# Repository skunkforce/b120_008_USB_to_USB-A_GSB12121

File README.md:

# edgy_board number b120
This design is part of the [edgy board project](https://github.com/skunkforce/edgy_boards). 

# getting started
This repository uses submodules. After cloning use the command 

```$ git submodule update --init --recursive```

to pull the submodules before opening the project with kicad. 

# Tests
Tests can be found in [TESTS.md](TESTS.md)

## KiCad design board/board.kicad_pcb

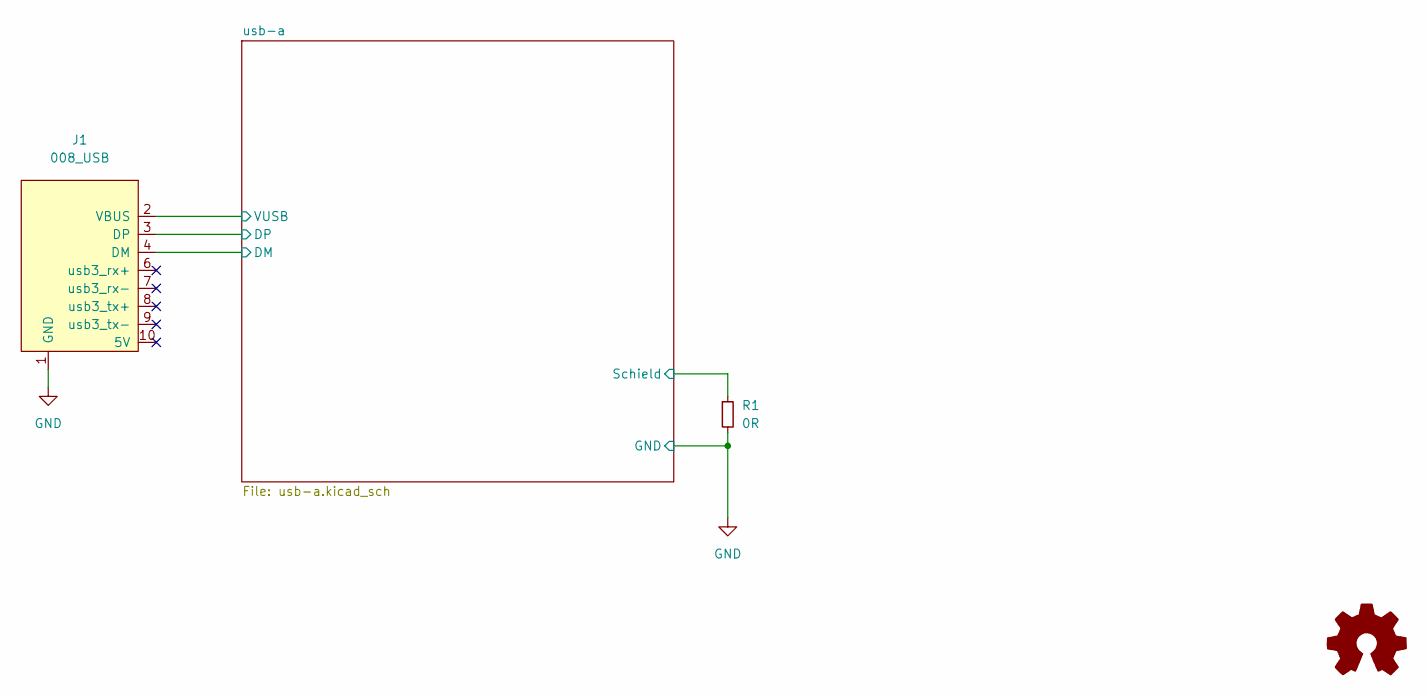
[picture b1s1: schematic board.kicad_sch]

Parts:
J1: 008_USB; on_edge_2x05_device
LOGO1: Logo_Open_Hardware_Small; OSHW-Symbol_6.7x6mm_SilkScreen
R1: 0R; R_0603_1608Metric

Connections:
/usb-a/DM: J1.4 (DM); also elsewhere on the board
/usb-a/DP: J1.3 (DP); also elsewhere on the board
/usb-a/Schield: R1.1; also elsewhere on the board
/usb-a/VUSB: J1.2 (VBUS); also elsewhere on the board
GND: J1.1 (GND), R1.2; also elsewhere on the board

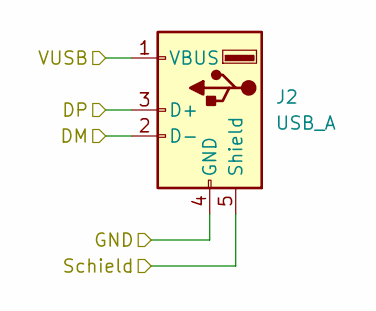
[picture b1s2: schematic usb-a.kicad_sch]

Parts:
J2: USB_A; USB_A_CONNFLY_DS1095-WNR0

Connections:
/usb-a/DM: J2.2 (D-); also elsewhere on the board
/usb-a/DP: J2.3 (D+); also elsewhere on the board
/usb-a/Schield: J2.5 (Shield); also elsewhere on the board
/usb-a/VUSB: J2.1 (VBUS); also elsewhere on the board
GND: J2.4 (GND); also elsewhere on the board

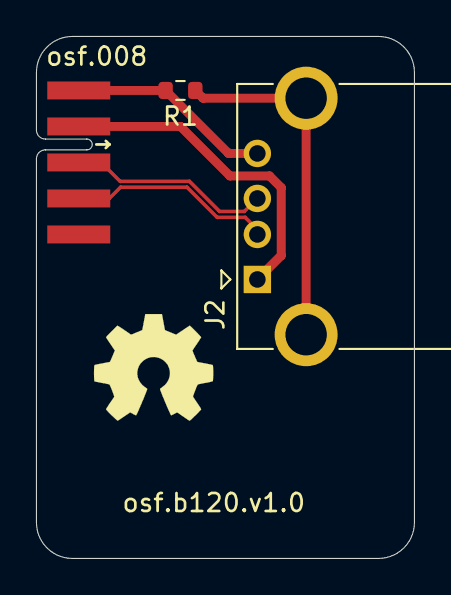
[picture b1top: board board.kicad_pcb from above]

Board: 2 copper layers, 21.0 x 29.0 mm, 4 parts (0 on the bottom side), 5 nets.

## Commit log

2023-03-29 initial
